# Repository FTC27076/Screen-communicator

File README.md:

# Screen-communicator
Ill find a better name

This is my final hack club half-life designer project, and since this is freestyle, I want to do something that I've always thought about:
It's an esp 32 connected to a screen and a joystick. You type with the joystick, and press the joystick switch so that it sends the messgage. Then, the ESP uses something called ESPNOW to send it to another screen device thing. This would allow you to have basically a text based walkie-talkie.

# Materials

1. 12864 LCD
2. Ky-023 analog joystick with switch
3. ESP32-S3-wroom-1
4. 4XAA battery holder
5. Boot, enable and power switch
6. PCB
7. CASE

## PCB

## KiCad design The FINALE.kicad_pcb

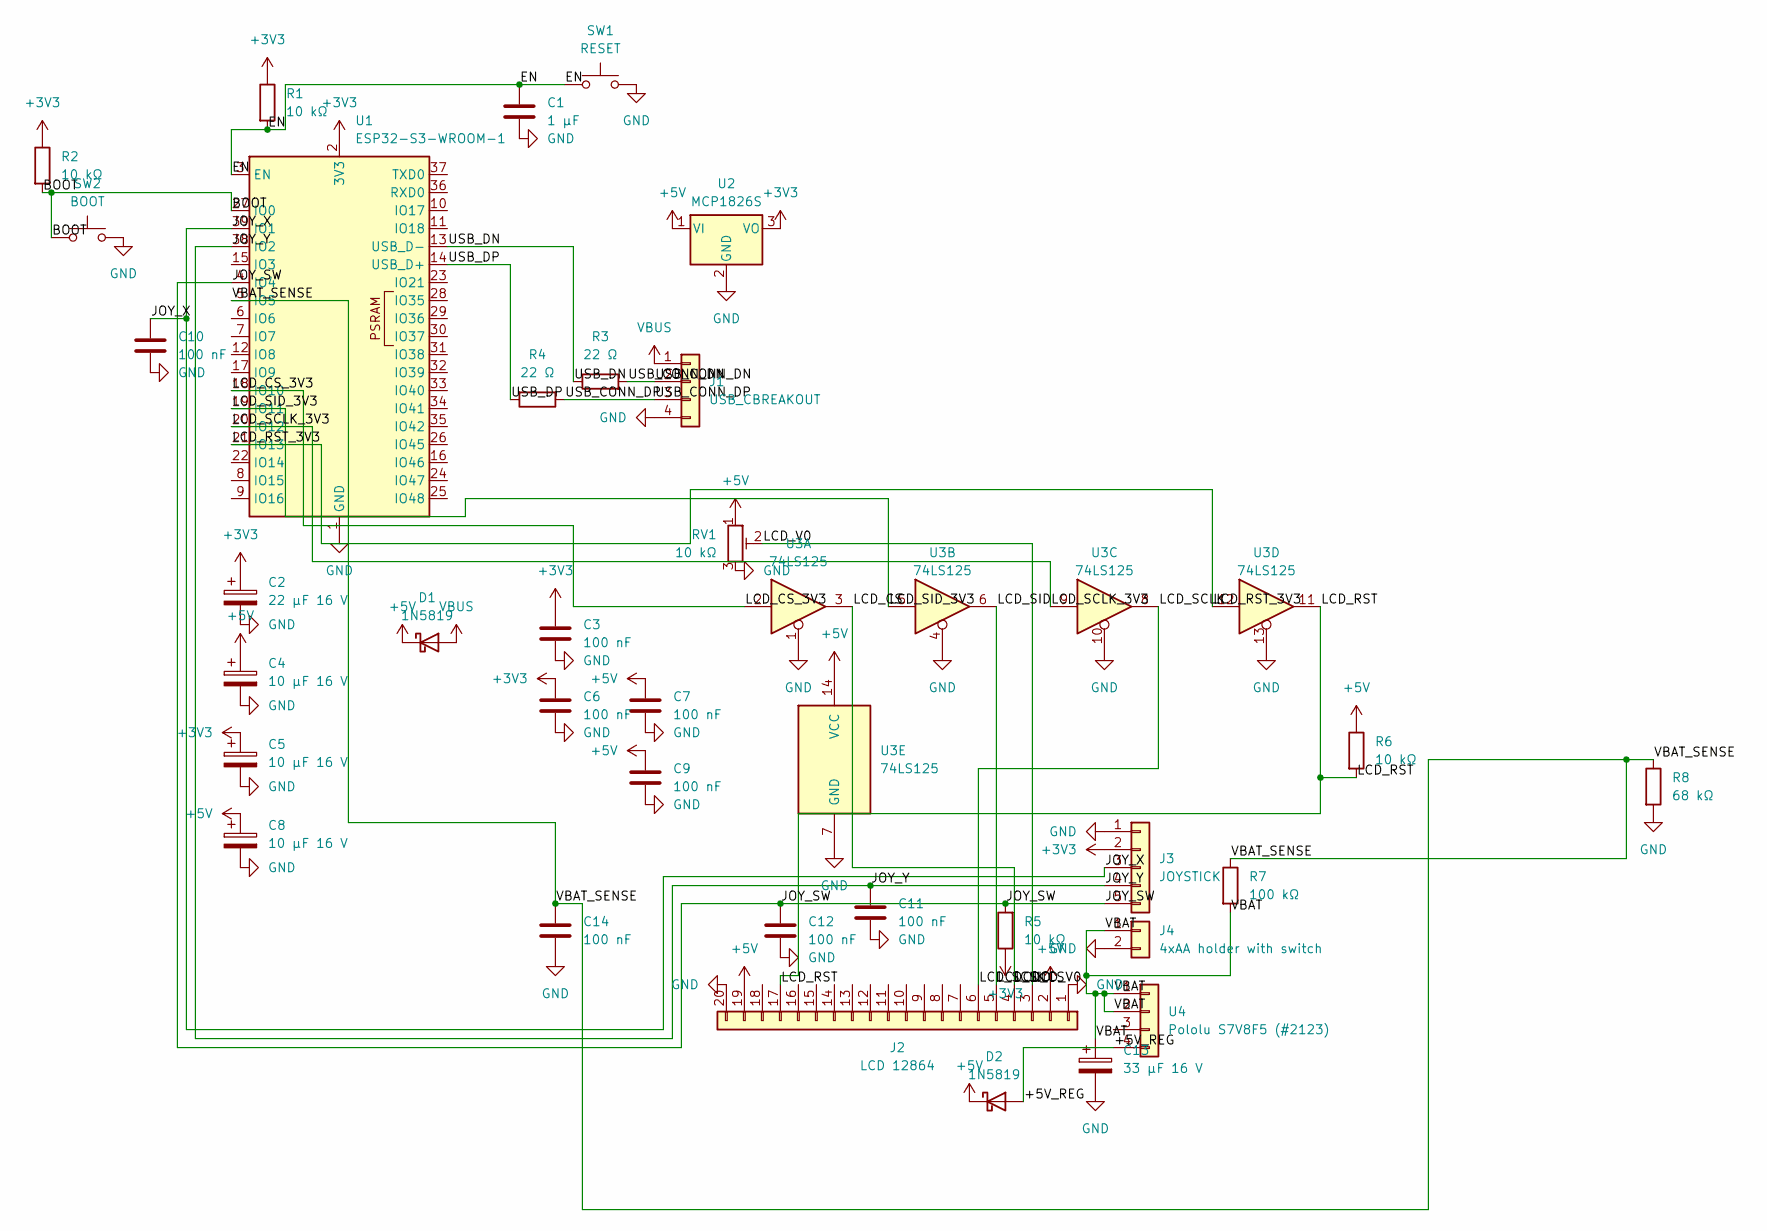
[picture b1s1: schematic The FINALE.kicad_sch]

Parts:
C1: 1 µF; C_Disc_D5.0mm_W2.5mm_P5.00mm
C2: 22 µF 16 V; CP_Radial_D5.0mm_P2.00mm
C3, C6, C7, C9, C10, C11, C12, C14: 100 nF; C_Disc_D3.0mm_W1.6mm_P2.50mm
C4, C5, C8: 10 µF 16 V; CP_Radial_D5.0mm_P2.00mm
C13: 33 µF 16 V; CP_Radial_D5.0mm_P2.00mm
D1, D2: 1N5819; D_DO-41_SOD81_P10.16mm_Horizontal
J1: USB_CBREAKOUT; Adafruit_4090_USB-C_Breakout_Socket
J2: LCD 12864; LCD_12864_ST7920_93x70_Socket
J3: JOYSTICK; Adafruit_512_Joystick_Breakout_Socket
J4: 4xAA holder with switch; JST_XH_B2B-XH-A_1x02_P2.50mm_Vertical
R1, R2, R5, R6: 10 kΩ; R_Axial_DIN0207_L6.3mm_D2.5mm_P7.62mm_Horizontal
R3, R4: 22 Ω; R_Axial_DIN0207_L6.3mm_D2.5mm_P7.62mm_Horizontal
R7: 100 kΩ; R_Axial_DIN0207_L6.3mm_D2.5mm_P7.62mm_Horizontal
R8: 68 kΩ; R_Axial_DIN0207_L6.3mm_D2.5mm_P7.62mm_Horizontal
RV1: 10 kΩ; Potentiometer_Bourns_3296W_Vertical
SW1: RESET; SW_PUSH_6mm
SW2: BOOT; SW_PUSH_6mm
U1: ESP32-S3-WROOM-1; ESP32-S3-WROOM-1ThermalVia0.3
U2: MCP1826S; TO-220-3_Horizontal_TabDown
U3: 74LS125; DIP-14_W7.62mm_Socket
U4: Pololu S7V8F5 (#2123); Pololu_S7V8F5_Socket

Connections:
+3V3: C2.1, C3.1, C5.1, C6.1, J3.2, R1.1, R2.1, R5.1, U1.2 (3V3), U2.3 (VO)
+5V: C4.1, C7.1, C8.1, C9.1, D1.1 (K), D2.1 (K), J2.2, J2.19, R6.1, RV1.1, U2.1 (VI), U3.14 (VCC)
/+5V_REG: D2.2 (A), U4.4
/BOOT: R2.2, SW2.1, U1.27 (IO0)
/EN: C1.1, R1.2, SW1.1, U1.3 (EN)
/JOY_SW: C12.1, J3.5, R5.2, U1.4 (IO4)
/JOY_X: C10.1, J3.3, U1.39 (IO1)
/JOY_Y: C11.1, J3.4, U1.38 (IO2)
/LCD_CS: J2.4, U3.3
/LCD_CS_3V3: U1.18 (IO10), U3.2
/LCD_RST: J2.17, R6.2, U3.11
/LCD_RST_3V3: U1.21 (IO13), U3.12
/LCD_SCLK: J2.6, U3.8
/LCD_SCLK_3V3: U1.20 (IO12), U3.9
/LCD_SID: J2.5, U3.6
/LCD_SID_3V3: U1.19 (IO11), U3.5
/LCD_V0: J2.3, RV1.2
/USB_CONN_DN: J1.2, R3.2
/USB_CONN_DP: J1.3, R4.1
/USB_DN: R3.1, U1.13 (USB_D-)
/USB_DP: R4.2, U1.14 (USB_D+)
/VBAT: C13.1, J4.1, R7.2, U4.1, U4.2
/VBAT_SENSE: C14.1, R7.1, R8.1, U1.5 (IO5)
GND: C1.2, C2.2, C3.2, C4.2, C5.2, C6.2, C7.2, C8.2, C9.2, C10.2, C11.2, C12.2, C13.2, C14.2, J1.4, J2.1, J2.20, J3.1, J4.2, R8.2, RV1.3, SW1.2, SW2.2, U1.1 (GND), U1.40 (GND), U1.41 (GND), U2.2 (GND), U3.1, U3.4, U3.7 (GND), U3.10, U3.13
VBUS: D1.2 (A), J1.1

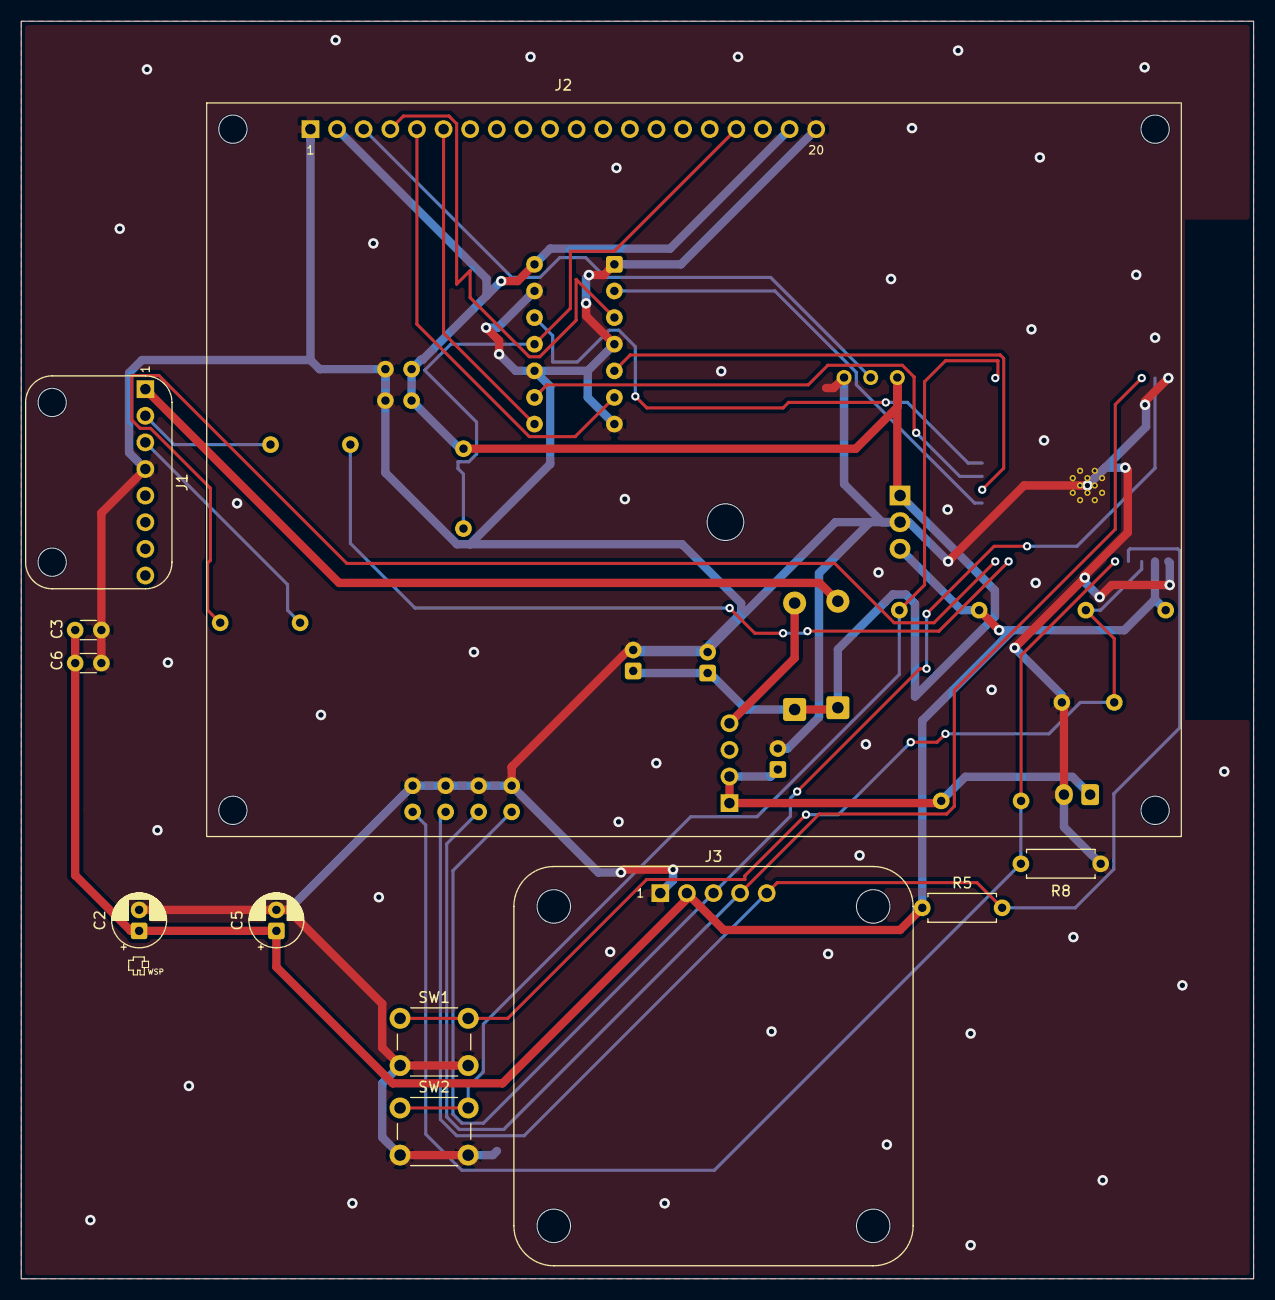
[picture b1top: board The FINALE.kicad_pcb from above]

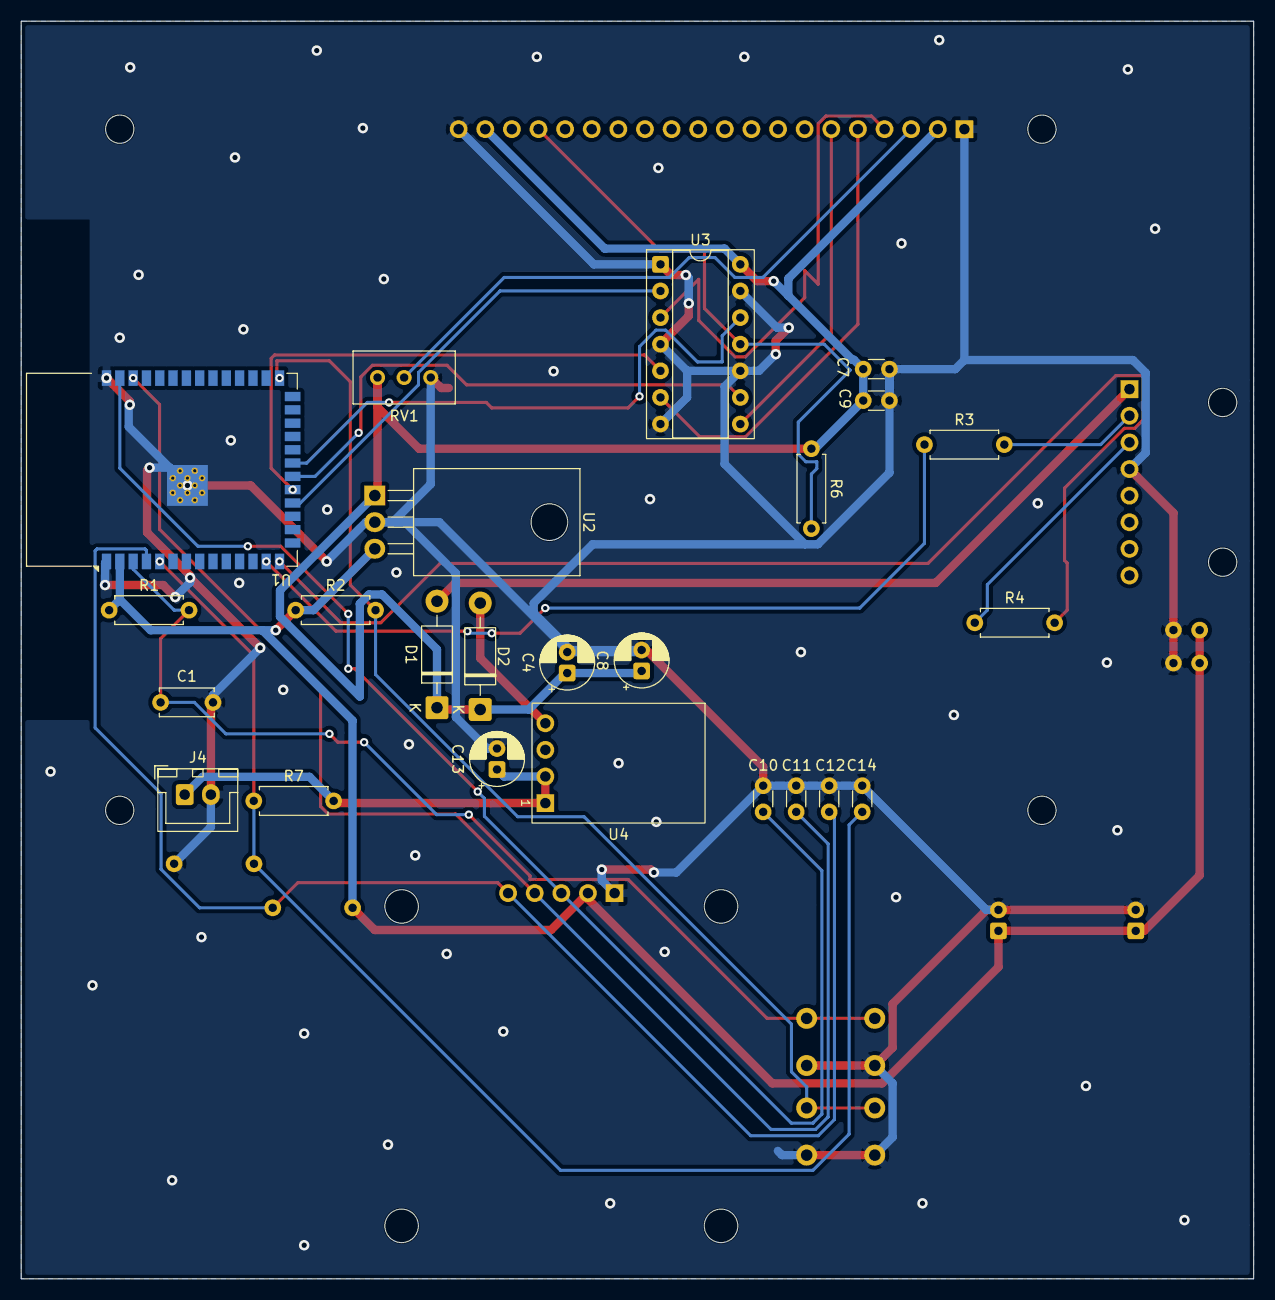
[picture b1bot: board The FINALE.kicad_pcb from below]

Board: 2 copper layers, 117.6 x 120.0 mm, 35 parts (24 on the bottom side), 25 nets.
